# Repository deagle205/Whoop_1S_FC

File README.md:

# Phil: 1S whoop flight controller (KiCad 10)

Three stacked 19x19 / 16x16 boards on a 12.8 mm M1.4 screw square:

- `Whoop_1S_FC.*`: flight controller (STM32G473 WLCSP-81, ICM-42688-P, SPL06, ELRS SX1281 + ESP8285, TPS63802)
- `Phil_ESC/`: 4-in-1 Bluejay ESC (4x EFM8BB51, 12x SiA517DJ)
- `Phil_VTX/`: 5.8 GHz VTX (RTC6705 + SE5004L), AT7456E OSD, blackbox flash, 5 V boost

Shared libraries: `WhoopFC.kicad_sym`, `WhoopFC.pretty/`, `WhoopFC.3dshapes/`.
Note: 3D model paths in the footprints are absolute (C:/Users/Survi/...), so other machines won't show them without editing.

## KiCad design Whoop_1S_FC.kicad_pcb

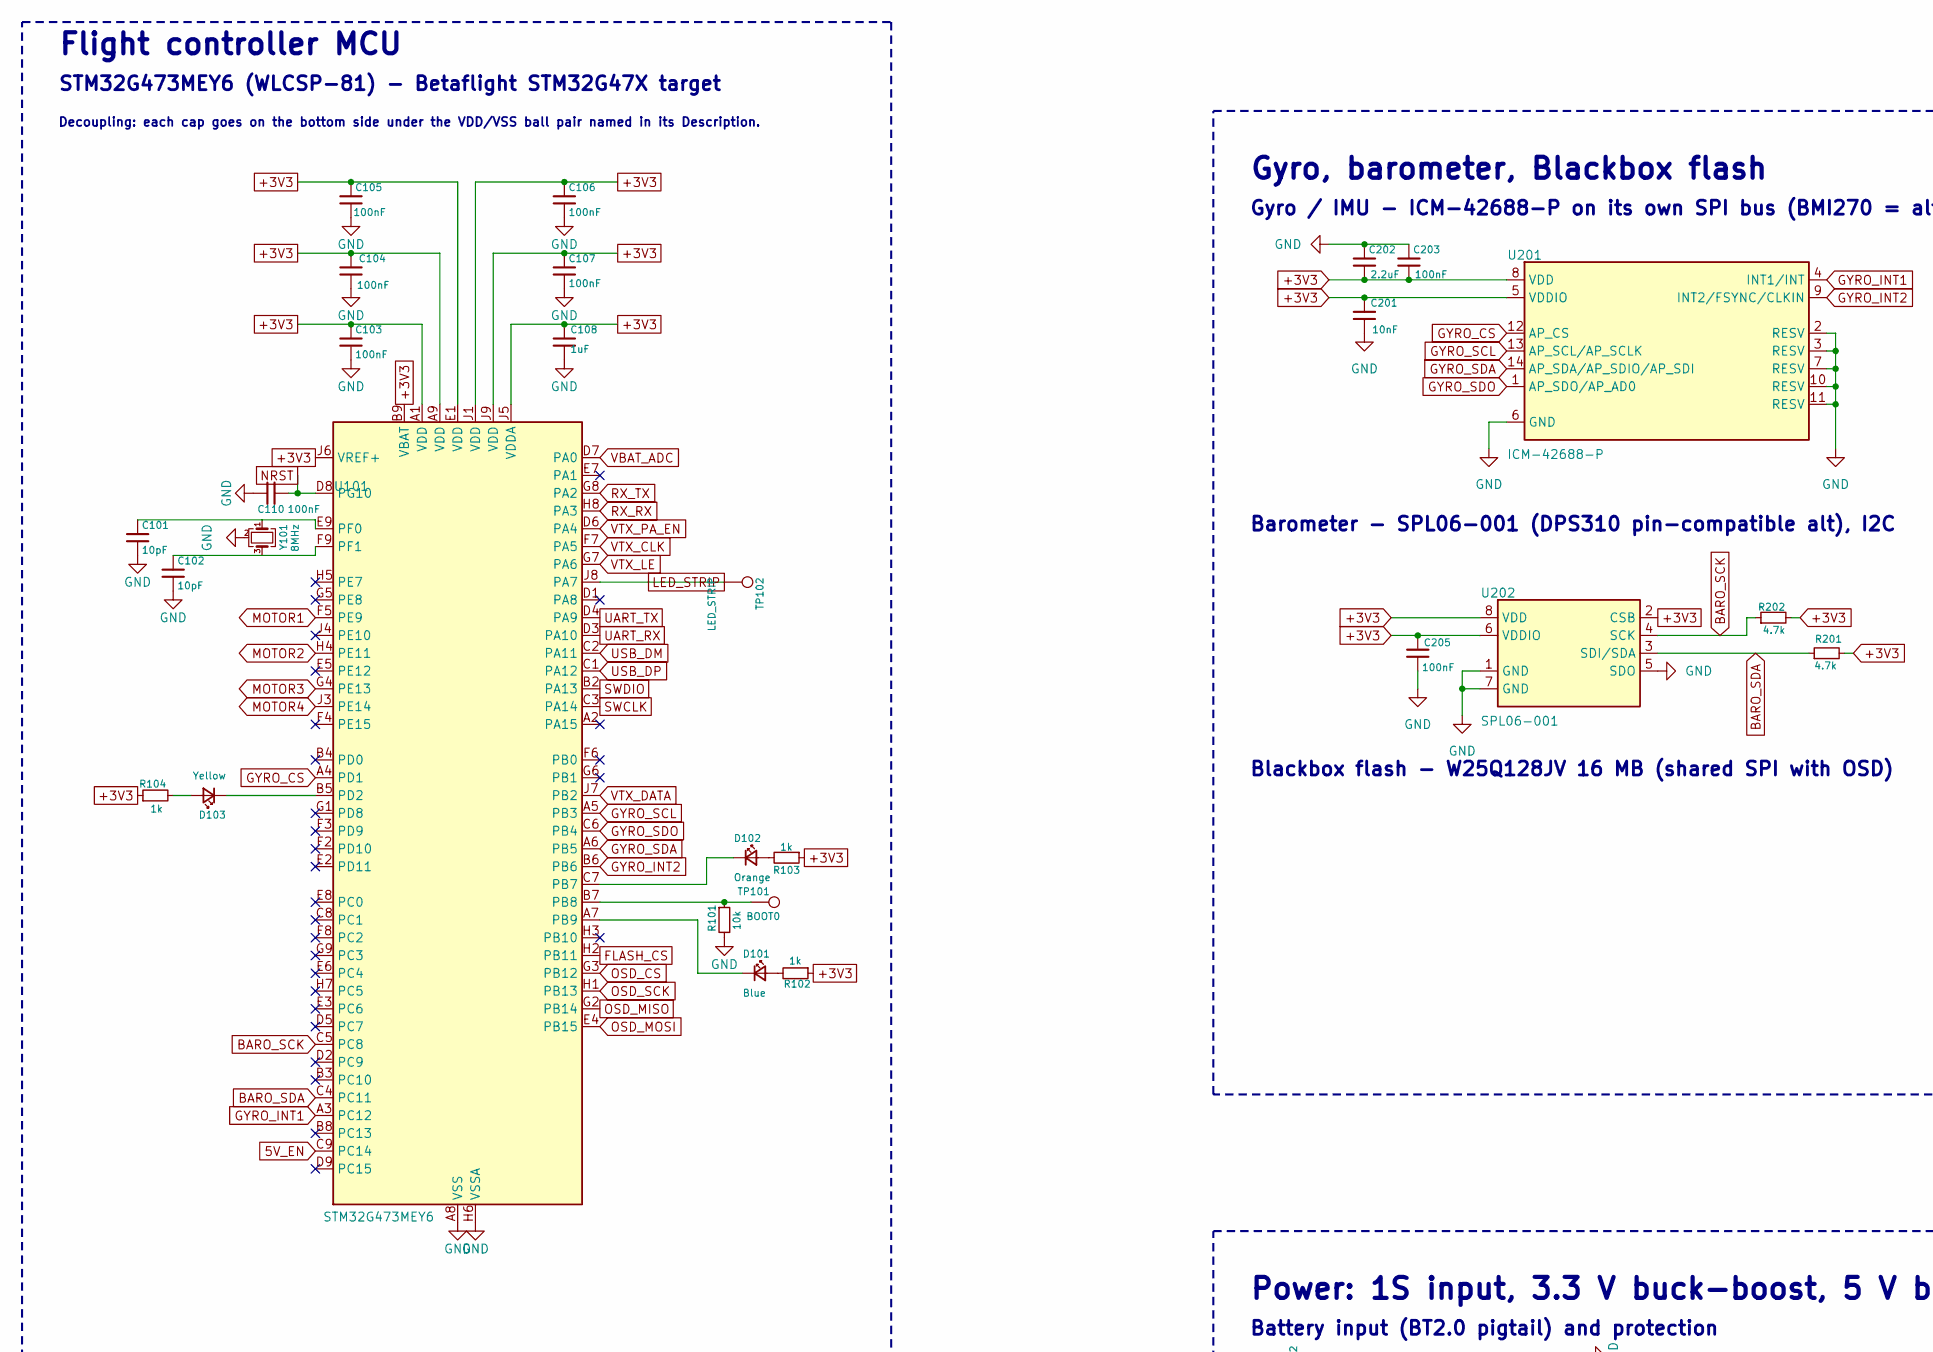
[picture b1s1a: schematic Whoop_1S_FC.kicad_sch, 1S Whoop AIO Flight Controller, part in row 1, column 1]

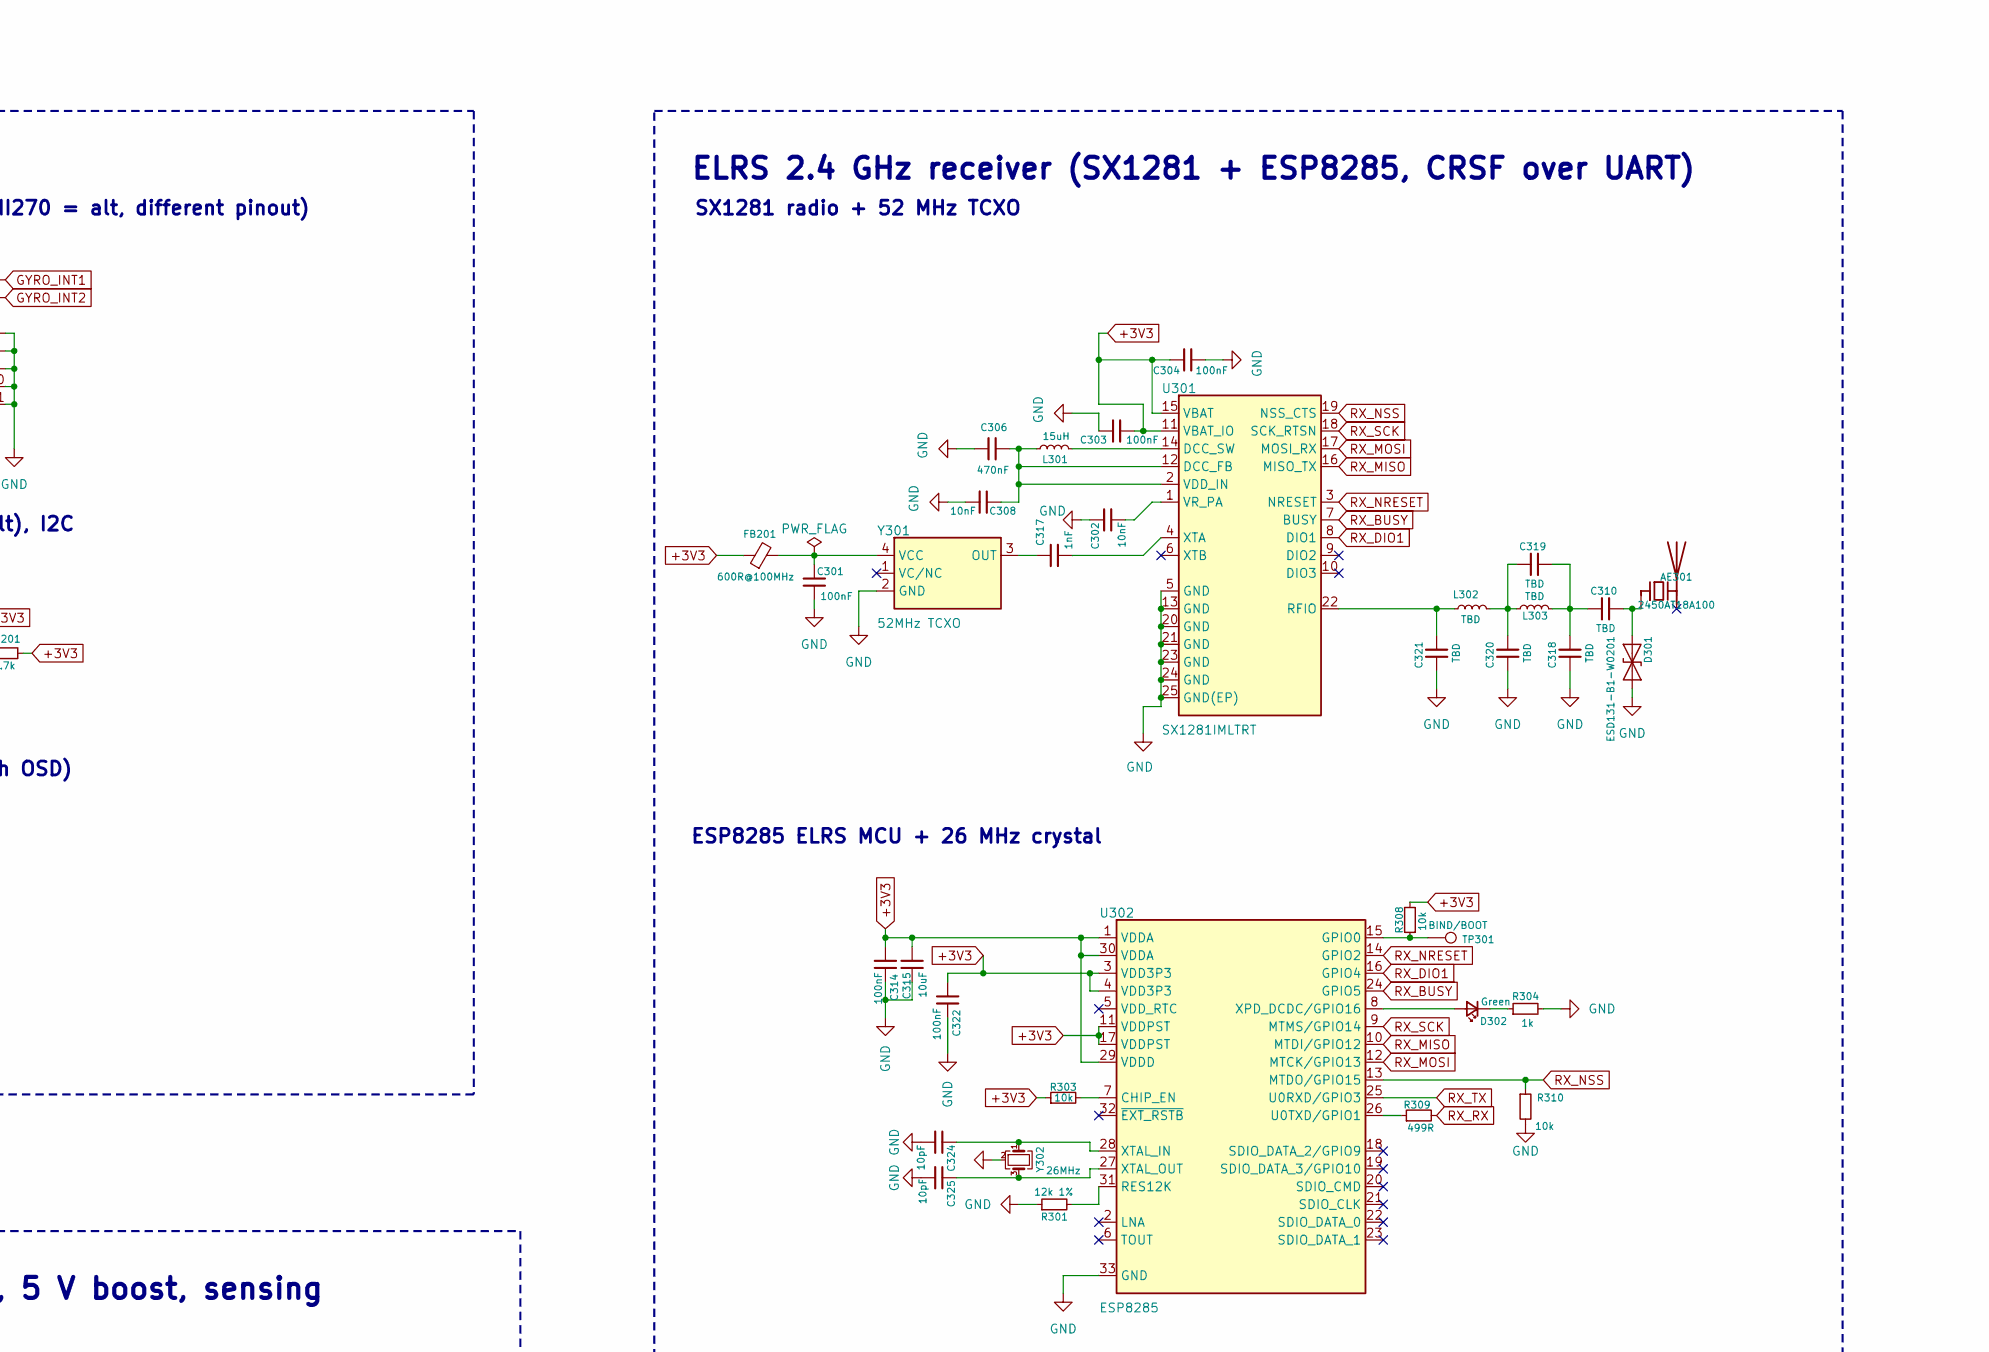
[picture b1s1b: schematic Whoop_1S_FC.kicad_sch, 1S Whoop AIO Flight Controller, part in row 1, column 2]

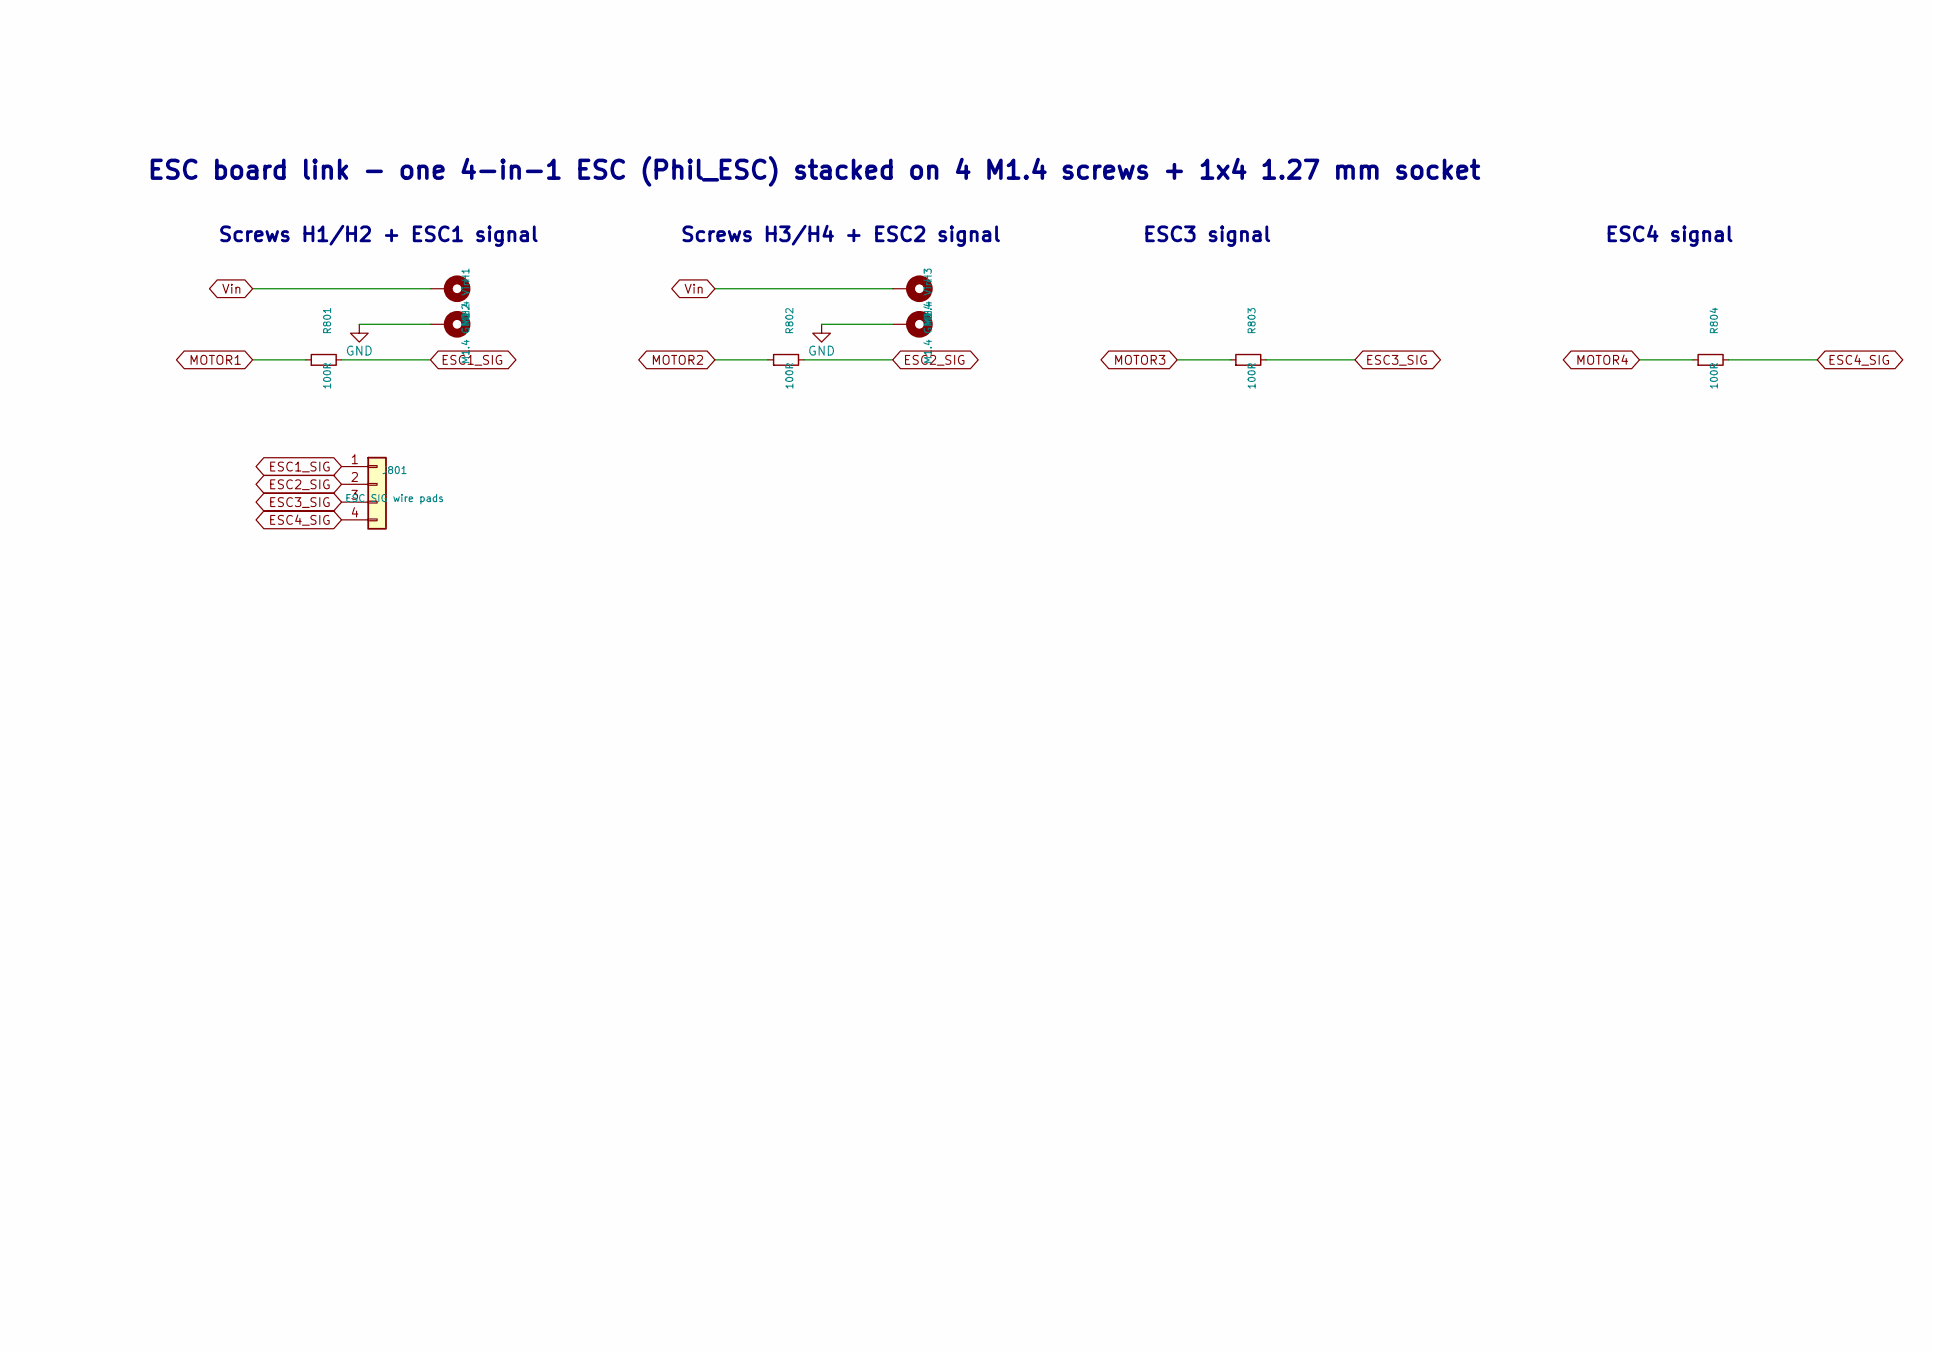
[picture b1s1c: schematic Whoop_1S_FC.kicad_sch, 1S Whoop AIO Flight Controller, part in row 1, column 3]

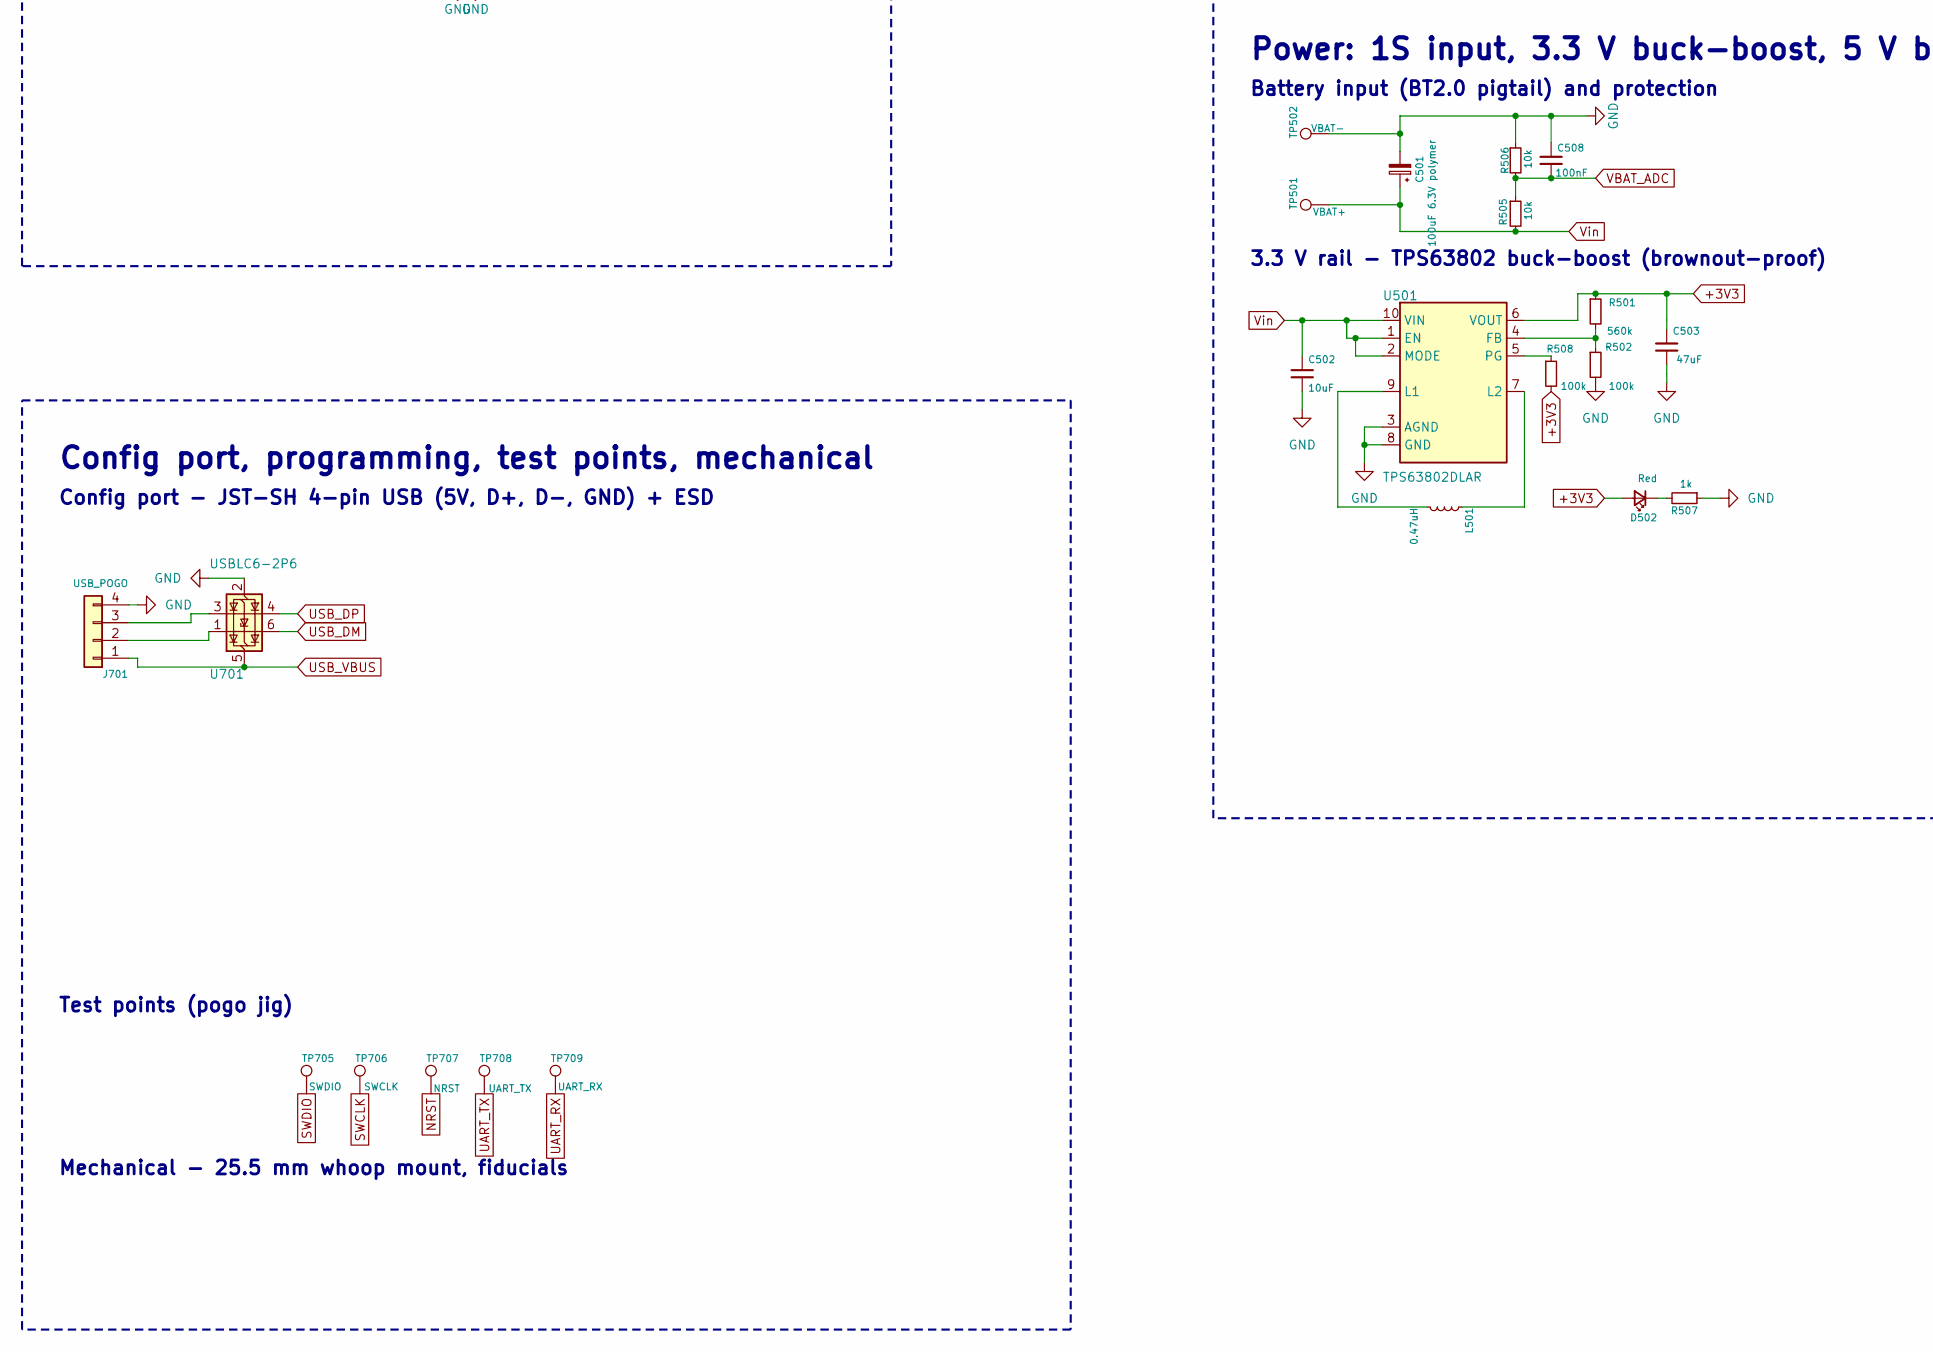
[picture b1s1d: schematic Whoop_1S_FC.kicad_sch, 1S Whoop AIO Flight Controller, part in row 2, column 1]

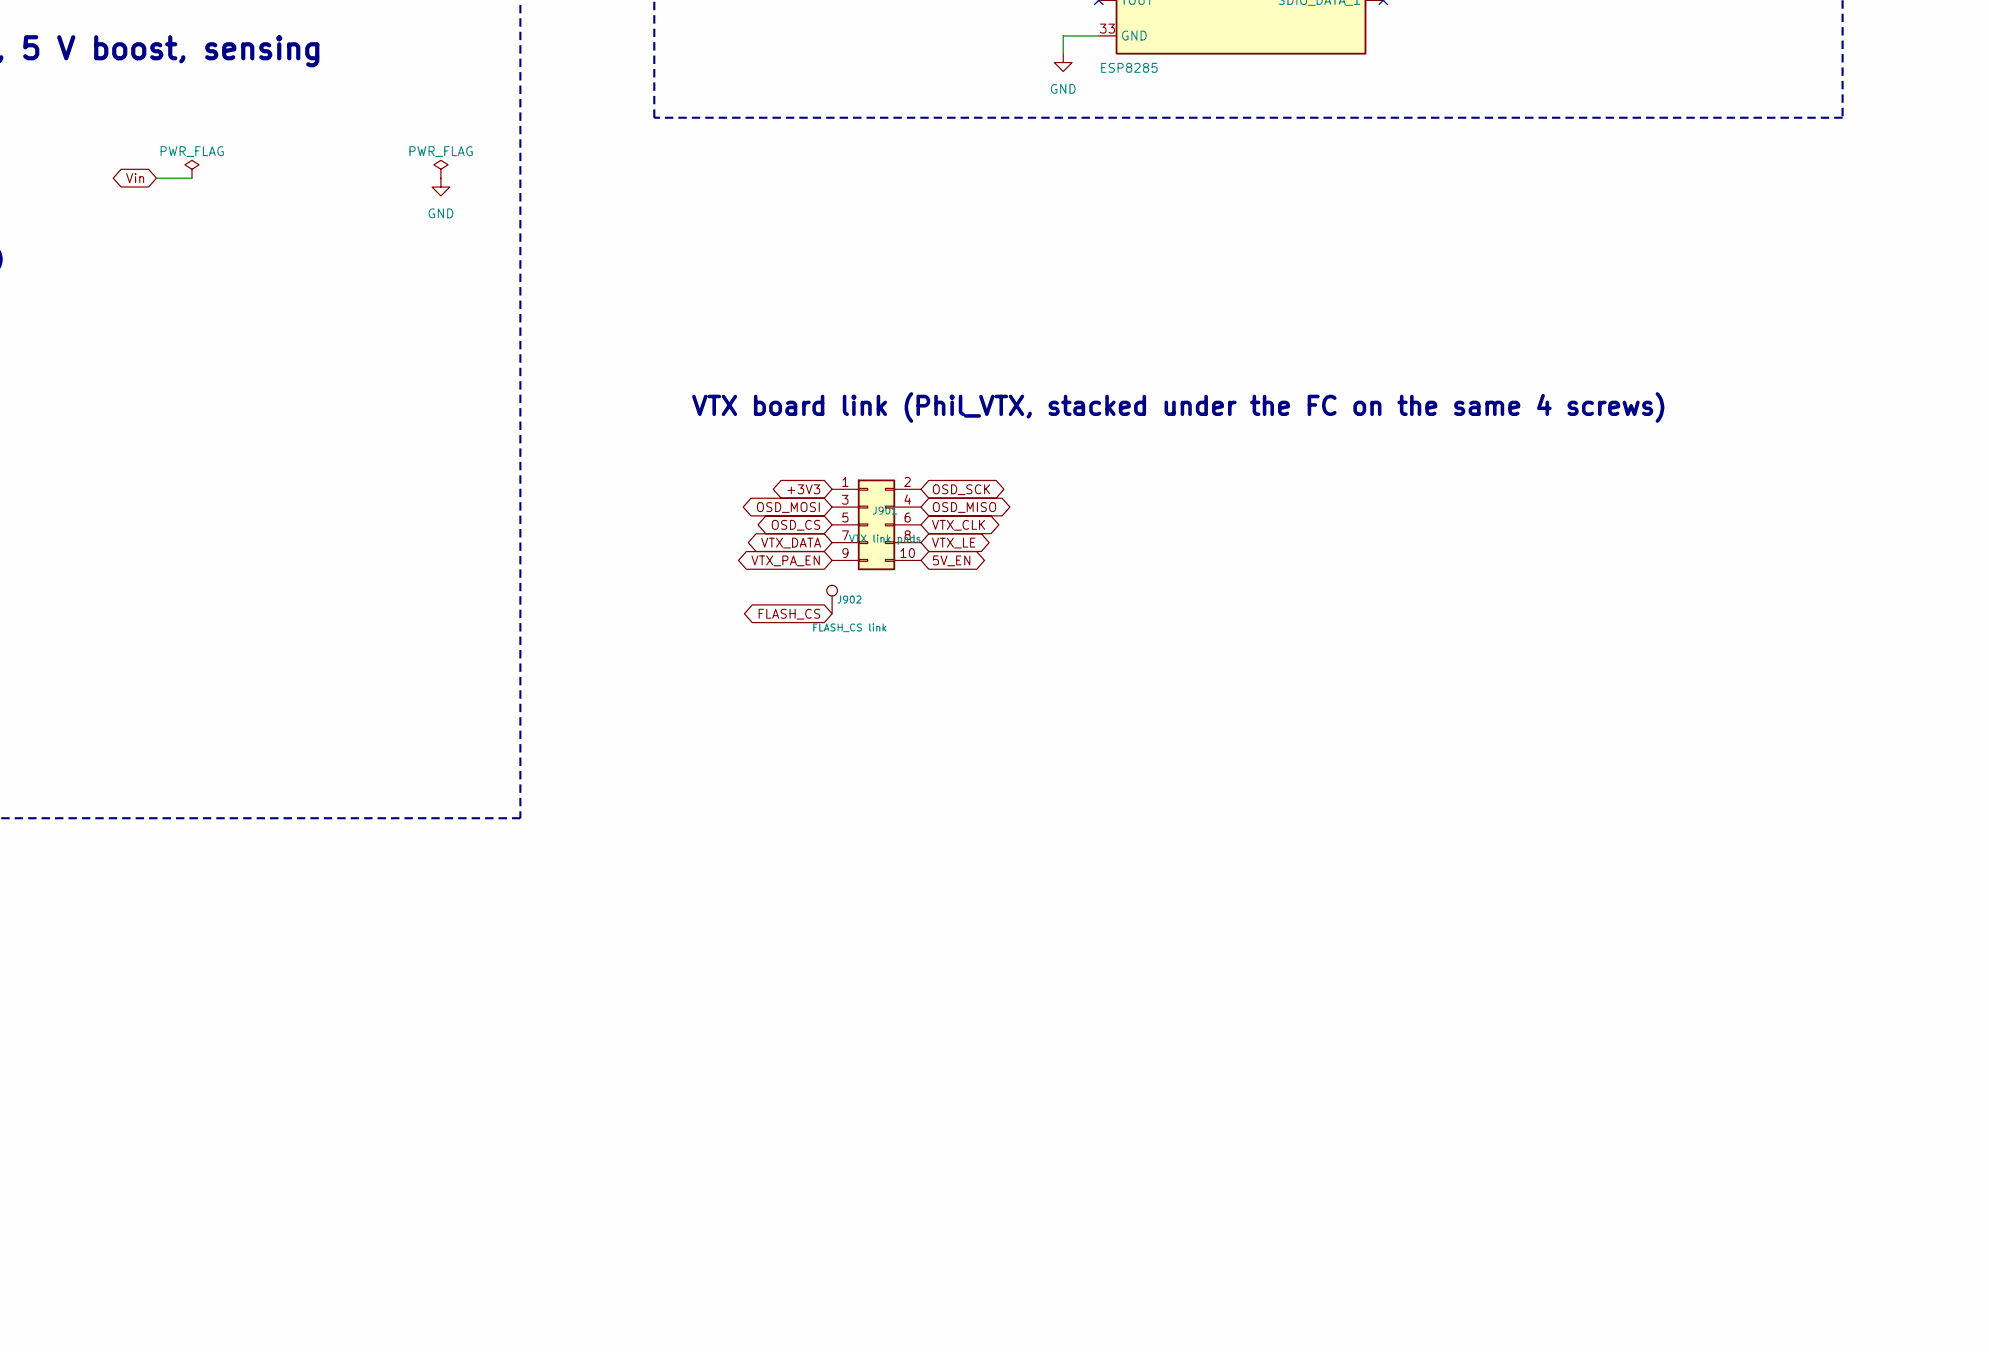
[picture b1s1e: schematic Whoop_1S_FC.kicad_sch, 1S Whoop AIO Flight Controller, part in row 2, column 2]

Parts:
AE301: 2450AT18A100; Johanson_2450AT18x100; MPN 2450AT18A100
C101, C102, C324, C325: 10pF; C_0201_0603Metric; MPN GRM0335C1H100JA01D; LCSC C76921
C103, C104, C105, C106, C107, C110, C203, C205, C301, C303, C304, C314, C322, C508: 100nF; C_0201_0603Metric; MPN CL03A104KQ3NNNC; LCSC C160831
C108: 1uF; C_0201_0603Metric; MPN CL03A105MQ3CSNC; LCSC C170152
C201, C302, C308: 10nF; C_0201_0603Metric; MPN GRM033R71A103KA01D; LCSC C76941
C202: 2.2uF; C_0201_0603Metric; MPN CL03A225MQ3CRNC; LCSC C77762
C306: 470nF; C_0201_0603Metric; MPN CL03A474KQ3NNNC; LCSC C318543
C310, C318, C319, C320, C321: TBD; C_0201_0603Metric
C315, C502: 10uF; C_0603_1608Metric; MPN CL10A106KP8NNNC; LCSC C19702
C317: 1nF; C_0201_0603Metric; MPN GRM033R71E102KA01D; LCSC C76943
C501: 100uF 6.3V polymer; CP_EIA-3216-18_Kemet-A
C503: 47uF; C_0603_1608Metric; MPN GRM188R60J476ME15
D101: Blue; LED_0201_0603Metric
D102: Orange; LED_0201_0603Metric
D103: Yellow; LED_0201_0603Metric
D301: ESD131-B1-W0201; Infineon_SG-WLL-2-3_0.58x0.28_P0.36mm; MPN ESD131-B1-W0201
D302: Green; LED_0201_0603Metric
D502: Red; LED_0201_0603Metric
FB201: 600R@100MHz; L_0402_1005Metric
H1, H3: M1.4 Vin; MountingHole_1.6mm_M1.4_Pad_2.6mm
H2, H4: M1.4 GND; MountingHole_1.6mm_M1.4_Pad_2.6mm
J701: USB_POGO; Pogo_1x04_P1.27mm_D0.9mm; MPN SM04B-SRSS-TB
J801: ESC SIG wire pads; Pads_1x04_P1.8mm_1.5x2.0mm
J901: VTX link pads; Pads_2x05_P1.8mm_1.5x2.0mm
J902: FLASH_CS link; TP_Wire_1.5x2.0mm
L301: 15uH; L_0603_1608Metric
L302, L303: TBD; L_0201_0603Metric
L501: 0.47uH; L_Murata_DFE201610P
R101, R303, R308, R310, R505, R506: 10k; R_0201_0603Metric; MPN RC0201FR-0710KL; LCSC C106225
R102, R103, R104, R304, R507: 1k; R_0201_0603Metric; MPN 0201WMF1001TEE; LCSC C270365
R201, R202: 4.7k; R_0201_0603Metric; MPN 0201WMF4701TEE; LCSC C270346
R301: 12k 1%; R_0201_0603Metric; MPN RC0201FR-0712KL; LCSC C295719
R309: 499R; R_0201_0603Metric; MPN RC0201FR-07499RL; LCSC C138137
R501: 560k; R_0201_0603Metric; MPN RC0201DR-07560KL; LCSC C2111026
R502, R508: 100k; R_0201_0603Metric; MPN 0201WMF1003TEE; LCSC C270364
R801, R802, R803, R804: 100R; R_0201_0603Metric; MPN 0201WMF1000TEE; LCSC C270366
TP101: BOOT0; TP_Probe_D0.6mm
TP102: LED_STRIP; TP_Wire_1.5x2.0mm
TP301: BIND/BOOT; TP_Probe_D0.6mm
TP501: VBAT+; TP_Battery_1.5x2.2mm
TP502: VBAT-; TP_Battery_1.5x2.2mm
TP705: SWDIO; TP_Probe_D0.6mm
TP706: SWCLK; TP_Probe_D0.6mm
TP707: NRST; TP_Probe_D0.6mm
TP708: UART_TX; TP_Probe_D0.6mm
TP709: UART_RX; TP_Probe_D0.6mm
U101: STM32G473MEY6; ST_WLCSP-81_4.02x4.27mm_Layout9x9_P0.4mm; MPN STM32G473MEY6
U201: ICM-42688-P; Bosch_LGA-14_3x2.5mm_P0.5mm; MPN ICM-42688-P
U202: SPL06-001; Bosch_LGA-8_2x2.5mm_P0.65mm_ClockwisePinNumbering; MPN SPL06-001
U301: SX1281IMLTRT; QFN-24-1EP_4x4mm_P0.5mm_EP2.6x2.6mm; MPN SX1281IMLTRT
U302: ESP8285; QFN-32-1EP_5x5mm_P0.5mm_EP3.7x3.7mm; MPN ESP8285N08
U501: TPS63802DLAR; Texas_VSON-HR-10_2x3mm_P0.5mm_DLA0010A; MPN TPS63802DLAR
U701: USBLC6-2P6; SOT-666; MPN USBLC6-2SC6
Y101: 8MHz; Crystal_SMD_2016-4Pin_2.0x1.6mm
Y301: 52MHz TCXO; Oscillator_SMD_SiT_PQFN-4Pin_2.0x1.6mm
Y302: 26MHz; Crystal_SMD_WE_IQXC-26-4Pin_1.6x1.2mm

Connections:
5V_EN: J901.10, U101.C9 (PC14)
+3V3: C103.1, C104.1, C105.1, C106.1, C107.1, C108.1, C201.1, C202.2, C203.2, C205.1, C303.2, C304.1, C314.2, C315.1, C322.2, C503.1, D502.2 (A), FB201.1, J901.1, R102.1, R103.1, R104.1, R201.2, R202.2, R303.1, R308.2, R501.1, R508.2, U101.A1 (VDD), U101.A9 (VDD), U101.B9 (VBAT), U101.E1 (VDD), U101.J1 (VDD), U101.J5 (VDDA), U101.J6 (VREF+), U101.J9 (VDD), U201.5 (VDDIO), U201.8 (VDD), U202.2 (CSB), U202.6 (VDDIO), U202.8 (VDD), U301.11 (VBAT_IO), U301.15 (VBAT), U302.1 (VDDA), U302.3 (VDD3P3), U302.4 (VDD3P3), U302.11 (VDDPST), U302.17 (VDDPST), U302.29 (VDDD), U302.30 (VDDA), U501.6 (VOUT)
BARO_SCK: R202.1, U101.C5 (PC8), U202.4 (SCK)
BARO_SDA: R201.1, U101.C4 (PC11), U202.3 (SDI/SDA)
ESC1_SIG: J801.1, R801.2
ESC2_SIG: J801.2, R802.2
ESC3_SIG: J801.3, R803.2
ESC4_SIG: J801.4, R804.2
FLASH_CS: J902.1, U101.H2 (PB11)
GND: C101.2, C102.2, C103.2, C104.2, C105.2, C106.2, C107.2, C108.2, C110.2, C201.2, C202.1, C203.1, C205.2, C301.2, C302.1, C303.1, C304.2, C306.2, C308.2, C314.1, C315.2, C318.1, C320.1, C321.1, C322.1, C324.2, C325.2, C501.2, C502.2, C503.2, C508.1, D301.2 (A2), H2.1, H4.1, J701.4, R101.2, R301.1, R304.2, R310.2, R502.2, R506.1, R507.1, TP502.1 (1_1), U101.A8 (VSS), U101.B1 (VSS), U101.F1 (VSS), U101.H6 (VSSA), U101.H9 (VSS), U101.J2 (VSS), U201.2 (RESV), U201.3 (RESV), U201.6 (GND), U201.7 (RESV), U201.10 (RESV), U201.11 (RESV), U202.1 (GND), U202.5 (SDO), U202.7 (GND), U301.5 (GND), U301.13 (GND), U301.20 (GND), U301.21 (GND), U301.23 (GND), U301.24 (GND), U301.25 (GND(EP)), U302.33 (GND), U501.3 (AGND), U501.8 (GND), U701.2 (GND), Y101.2 (G), Y101.4 (G), Y301.2 (GND), Y302.2 (G), Y302.4 (G)
GYRO_CS: U101.A4 (PD1), U201.12 (AP_CS)
GYRO_INT1: U101.A3 (PC12), U201.4 (INT1/INT)
GYRO_INT2: U101.B6, U201.9 (INT2/FSYNC/CLKIN)
GYRO_SCL: U101.A5 (PB3), U201.13 (AP_SCL/AP_SCLK)
GYRO_SDA: U101.A6 (PB5), U201.14 (AP_SDA/AP_SDIO/AP_SDI)
GYRO_SDO: U101.C6 (PB4), U201.1 (AP_SDO/AP_AD0)
LED_STRIP: TP102.1 (1_1), U101.J8 (PA7)
MOTOR1: R801.1, U101.F5 (PE9)
MOTOR2: R802.1, U101.H4 (PE11)
MOTOR3: R803.1, U101.G4 (PE13)
MOTOR4: R804.1, U101.J3 (PE14)
NRST: C110.1, TP707.1 (1_1), U101.D8 (PG10)
unnamed: AE301.1 (FEED_1), C310.2, D301.1 (A1)
unnamed: C310.1, C318.2, C319.2, L303.2
unnamed: C319.1, C320.2, L302.2, L303.1
unnamed: D101.2 (A), R102.2
unnamed: D101.1 (K), U101.A7 (PB9)
unnamed: D102.2 (A), R103.2
unnamed: D102.1 (K), U101.C7 (PB7)
unnamed: D103.2 (A), R104.2
unnamed: D103.1 (K), U101.B5 (PD2)
unnamed: D302.2 (A), U302.8 (XPD_DCDC/GPIO16)
unnamed: D302.1 (K), R304.1
unnamed: D502.1 (K), R507.2
unnamed: J701.2, U701.1 (I/O1)
unnamed: J701.3, U701.3 (I/O2)
unnamed: R101.1, TP101.1 (1_1), U101.B7 (PB8)
unnamed: C101.1, U101.E9 (PF0), Y101.1
unnamed: C102.1, U101.F9 (PF1), Y101.3
unnamed: C306.1, C308.1, L301.1, U301.2 (VDD_IN), U301.12 (DCC_FB)
unnamed: L301.2, U301.14 (DCC_SW)
unnamed: C321.2, L302.1, U301.22 (RFIO)
unnamed: C302.2, U301.1 (VR_PA)
unnamed: C317.2, U301.4 (XTA)
unnamed: R303.2, U302.7 (CHIP_EN)
unnamed: R308.1, TP301.1 (1_1), U302.15 (GPIO0)
unnamed: R301.2, U302.31 (RES12K)
unnamed: R309.1, U302.26 (U0TXD/GPIO1)
unnamed: C324.1, U302.28 (XTAL_IN), Y302.1
unnamed: C325.1, U302.27 (XTAL_OUT), Y302.3
unnamed: R501.2, R502.1, U501.4 (FB)
unnamed: L501.2, U501.9 (L1)
unnamed: L501.1, U501.7 (L2)
unnamed: R508.1, U501.5 (PG)
unnamed: C317.1, Y301.3 (OUT)
unnamed: C301.1, FB201.2, Y301.4 (VCC)
OSD_CS: J901.5, U101.G3 (PB12)
OSD_MISO: J901.4, U101.G2 (PB14)
OSD_MOSI: J901.3, U101.E4 (PB15)
OSD_SCK: J901.2, U101.H1 (PB13)
RX_BUSY: U301.7 (BUSY), U302.24 (GPIO5)
RX_DIO1: U301.8 (DIO1), U302.16 (GPIO4)
RX_MISO: U301.16 (MISO_TX), U302.10 (MTDI/GPIO12)
RX_MOSI: U301.17 (MOSI_RX), U302.12 (MTCK/GPIO13)
RX_NRESET: U301.3 (NRESET), U302.14 (GPIO2)
RX_NSS: R310.1, U301.19 (NSS_CTS), U302.13 (MTDO/GPIO15)
RX_RX: R309.2, U101.H8 (PA3)
RX_SCK: U301.18 (SCK_RTSN), U302.9 (MTMS/GPIO14)
RX_TX: U101.G8 (PA2), U302.25 (U0RXD/GPIO3)
SWCLK: TP706.1 (1_1), U101.C3 (PA14)
SWDIO: TP705.1 (1_1), U101.B2 (PA13)
UART_RX: TP709.1, U101.D3 (PA10)
UART_TX: TP708.1, U101.D4 (PA9)
USB_DM: U101.C2 (PA11), U701.6 (I/O1)
USB_DP: U101.C1 (PA12), U701.4 (I/O2)
USB_VBUS: J701.1, U701.5 (VBUS)
VBAT_ADC: C508.2, R505.1, R506.2, U101.D7 (PA0)
VTX_CLK: J901.6, U101.F7 (PA5)
VTX_DATA: J901.7, U101.J7 (PB2)
VTX_LE: J901.8, U101.G7 (PA6)
VTX_PA_EN: J901.9, U101.D6 (PA4)
Vin: C501.1, C502.1, H1.1, H3.1, R505.2, TP501.1 (1_1), U501.1 (EN), U501.2 (MODE), U501.10 (VIN)

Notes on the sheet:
Mechanical - 25.5 mm whoop mount, fiducials
Flight controller MCU
Config port, programming, test points, mechanical
Gyro, barometer, Blackbox flash
STM32G473MEY6 (WLCSP-81) - Betaflight STM32G47X target
3.3 V rail - TPS63802 buck-boost (brownout-proof)
Power: 1S input, 3.3 V buck-boost, 5 V boost, sensing
ESP8285 ELRS MCU + 26 MHz crystal
Test points (pogo jig)
Barometer - SPL06-001 (DPS310 pin-compatible alt), I2C
Config port - JST-SH 4-pin USB (5V, D+, D-, GND) + ESD
ELRS 2.4 GHz receiver (SX1281 + ESP8285, CRSF over UART)
Gyro / IMU - ICM-42688-P on its own SPI bus (BMI270 = alt, different pinout)
Screws H1/H2 + ESC1 signal
SX1281 radio + 52 MHz TCXO
ESC3 signal
VTX board link (Phil_VTX, stacked under the FC on the same 4 screws)
Screws H3/H4 + ESC2 signal
Decoupling: each cap goes on the bottom side under the VDD/VSS ball pair named in its Description.
ESC board link - one 4-in-1 ESC (Phil_ESC) stacked on 4 M1.4 screws + 1x4 1.27 mm socket
ESC4 signal
Battery input (BT2.0 pigtail) and protection
Blackbox flash - W25Q128JV 16 MB (shared SPI with OSD)

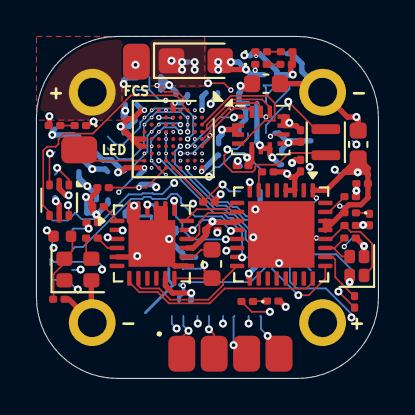
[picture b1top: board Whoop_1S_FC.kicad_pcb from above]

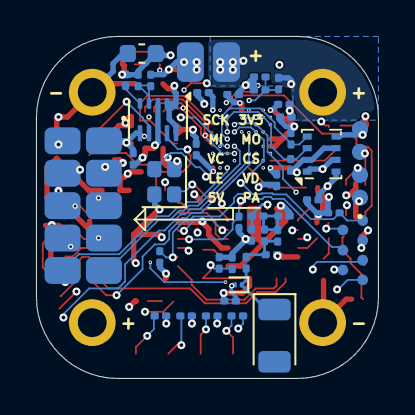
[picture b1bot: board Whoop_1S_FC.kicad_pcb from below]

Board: 6 copper layers, 19.0 x 19.0 mm, 96 parts (50 on the bottom side), 82 nets.
